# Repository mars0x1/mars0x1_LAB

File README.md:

# mars0x1_LAB — Mixed-Signal Electronics Workstation

An all-in-one, 4-layer mixed-signal laboratory instrument designed around the **ESP32-S3** microcontroller. `mars0x1_LAB` integrates a **4-channel analog oscilloscope front-end**, an **AD9833 12.5 MHz Direct Digital Synthesis (DDS) function generator**, a **dual high-speed pulse generator**, **3× rotary encoder physical user controls**, and an ultra-low-noise **100% linear split power supply**.

---

---

## ⚡ Technical Specifications

| Subsystem | Specification | Value / Details |
| :--- | :--- | :--- |
| **Physical Dimensions** | Board Size | $175.59\,\text{mm} \times 134.00\,\text{mm}$ ($6.91^{\prime\prime} \times 5.28^{\prime\prime}$) |
| | Layer Stackup | 4 Copper Layers (`F.Cu`, `In1.Cu`, `In2.Cu`, `B.Cu`) |
| | Grounding & Thermal | 4-layer solid DGND planes with **220 DGND ground stitching vias** |
| | Fabrication Rules | Min $0.25\,\text{mm}$ trace, $0.20\,\text{mm}$ clearance, $0.30\,\text{mm}$ via drill (JLCPCB-ready) |
| **Core Controller** | Microcontroller | **ESP32-S3-DEVKITC-1-N8R2** |
| | Processor | Xtensa® 32-bit LX7 dual-core up to $240\,\text{MHz}$ |
| | Memory & Wireless | 8 MB Octal Flash, 2 MB PSRAM, Wi-Fi 4 (802.11 b/g/n), Bluetooth® 5 (LE) |
| | Host Interface | Dual USB-C: Native USB-OTG high-speed telemetry + CP2102/CH343 UART programming |
| **4-Channel Oscilloscope** | Channels | 4 Independent BNC Inputs (`CH 1`, `CH 2`, `CH 3`, `CH 4`) |
| | Analog Buffer | `U6` (`OPA4192IPWR`) — Precision Rail-to-Rail I/O, $10\,\text{MHz}$ GBW, $20\,\text{V}/\mu\text{s}$ slew rate, $5.5\,\text{nV}/\sqrt{\text{Hz}}$ ultra-low noise |
| | Precision Reference | `U10` (`REF3025AIDBZT`) — $2.50\,\text{V}$ voltage reference ($50\,\text{ppm}/^\circ\text{C}$) |
| | Input Protection | 4× $1\,\text{k}\Omega$ series current limiters (`R32`–`R35`) + 4× `BAT54S` Schottky clamping diodes (`D9`–`D12`) to $3.3\,\text{V}$ & DGND |
| **DDS Function Generator** | Core IC | Analog Devices AD9833 (28-bit frequency accumulator, $0.1\,\text{Hz}$ to $12.5\,\text{MHz}$) |
| | Module Sockets | Dual parallel female headers (`J5` Standard & `J12` Swapped CS/SDATA pinout) |
| | Waveforms | Sine, Triangle, Square (programmable via SPI) |
| | Output Driver | `U20` (`MCP4131`) digital potentiometer + `U9` (`TL071`) buffer + `TIP31C`/`TIP32C` complementary push-pull driver capable of driving $50\,\Omega$ loads |
| **Dual Pulse Generator** | Outputs | `PULSE 1` (`J11`) and `PULSE 2` (`J10`) via $75\,\Omega$ BNC connectors |
| | Drivers | Discrete NPN emitter-follower buffers (`Q1`, `Q4` `2N3904`) powered by $+5\,\text{V}$ |
| | Duty & Width | ESP32 hardware timers (MCPWM/LEDC) on clean GPIOs 47 & 21 |
| | Amplitude Control | `U8` (`MCP4131`) digital potentiometer + $1\,\text{k}\Omega$ emitter pull-downs (`R36`, `R37`) |
| **Front Panel Controls** | Rotary Encoders | 3× ALPS EC11 Encoders with Push Switches (`U17` TIME, `U18` VOLT, `U19` MENU) |
| **Power Supply (100% Linear)** | AC Input | 3-terminal pads (`J6`, `J7`, `J8`) for external center-tapped $12\text{V}-0-12\text{V}$ AC transformer secondary |
| | Rectification & Bulk | 6A full-wave bridge rectifier (`D1`–`D4` `6A10`) + $4000\,\mu\text{F}$ reservoir (`C1`–`C4`) |
| | Voltage Regulators | $+12\,\text{V}$ (`LM7812`), $-12\,\text{V}$ (`LM7912`), $+5\,\text{V}$ (`LM7805`) |
| | Noise & Ripple | Zero switching hash, pure analog linear regulation |

---

## 🎛️ Front Panel & Connector Mapping

All front-panel connectors along the bottom edge ($Y \approx 185.5\,\text{mm}$) are clearly ordered and labeled on the silkscreen from left to right:

```
+----------------------------------------------------------------------------------------------------+
|  [J11]       [J10]       [J9]          [U19]         [U18]         [U17]     [J1]   [J2]   [J3]   [J4]   |
| PULSE 1     PULSE 2    DDS OUT     ENC 3 (MENU)  ENC 2 (VOLT)  ENC 1 (TIME)  CH 1   CH 2   CH 3   CH 4   |
+----------------------------------------------------------------------------------------------------+
```

---

## 🔌 Power & Safety Instructions

> [!IMPORTANT]
> **External Low-Voltage AC Transformer Only — DO NOT CONNECT MAINS (120V / 240V)!**
> * Terminals `J6`, `J7`, and `J8` connect exclusively to the **low-voltage secondary side** of an external center-tapped transformer ($12\text{V}-0-12\text{V}$ AC, 20VA to 50VA).
> * `J8` = `~12V AC` (Secondary Leg 1)
> * `J7` = `0V CT` (Secondary Center Tap / Earth DGND)
> * `J6` = `~12V AC` (Secondary Leg 2)
> * The ESP32 DevKit is powered via USB Type-C from your host PC.

> [!WARNING]
> **TO-220 Tab Isolation:**
> * `LM7812` & `LM7805` tabs are connected to **DGND**.
> * `LM7912` tab is connected to **$-18\,\text{V}$ DC raw input**, NOT ground!
> * `TIP31C` & `TIP32C` tabs are connected to $+12\text{V}$ and $-12\text{V}$ collectors.
> * Always use **individual clip-on heatsinks** or insulating Sil-Pads and shoulder washers if mounting to a shared metal bracket.

---

## 📁 Repository Structure

```text
mars0x1_LAB/
├── assets/
│   ├── pcb_3d_render.png          # High-resolution 3D raytraced preview
│   ├── pcb_front.svg              # Top copper and silkscreen vector
│   ├── pcb_back.svg               # Bottom copper and silkscreen vector
│   ├── schematic_diagram.svg      # A3 schematic vector export
│   └── schematic.pdf              # Full production schematic PDF
├── gerbers/                       # Raw RS-274X Gerber & Excellon drill files
├── gerbers.zip                    # Ready-to-upload archive for JLCPCB
├── mars0x1_LAB.kicad_pro          # KiCad 9 Project file
├── mars0x1_LAB.kicad_sch          # KiCad 9 Schematic
├── mars0x1_LAB.kicad_pcb          # KiCad 9 PCB Layout
├── .gitignore
├── LICENSE                        # MIT License
└── README.md
```

---

## 🛠️ How to Order on JLCPCB

1. Download [`gerbers.zip`](gerbers.zip).
2. Go to [JLCPCB.com](https://jlcpcb.com) and click **Order Now**.
3. Drag and drop `gerbers.zip`.
4. Choose the following standard parameters:
   * **Layers:** 4
   * **Dimensions:** $175.59 \times 134.00\,\text{mm}$ (auto-detected)
   * **PCB Thickness:** 1.6 mm
   * **PCB Color:** Green / Blue / Black / Purple (user choice)
   * **Surface Finish:** HASL with lead (or ENIG for gold-plated pads)
   * **Copper Weight:** 1 oz outer / 0.5 oz inner
5. Submit order (Total cost for 5 boards fits well within the **$100 Hack Club OnBoard grant**).

---

## 📜 Credits & License

* **Designed by:** `mars0x1`
* **Sponsorship:** Built with support from [Hack Club](https://hackclub.com).
* **License:** [MIT License](LICENSE).

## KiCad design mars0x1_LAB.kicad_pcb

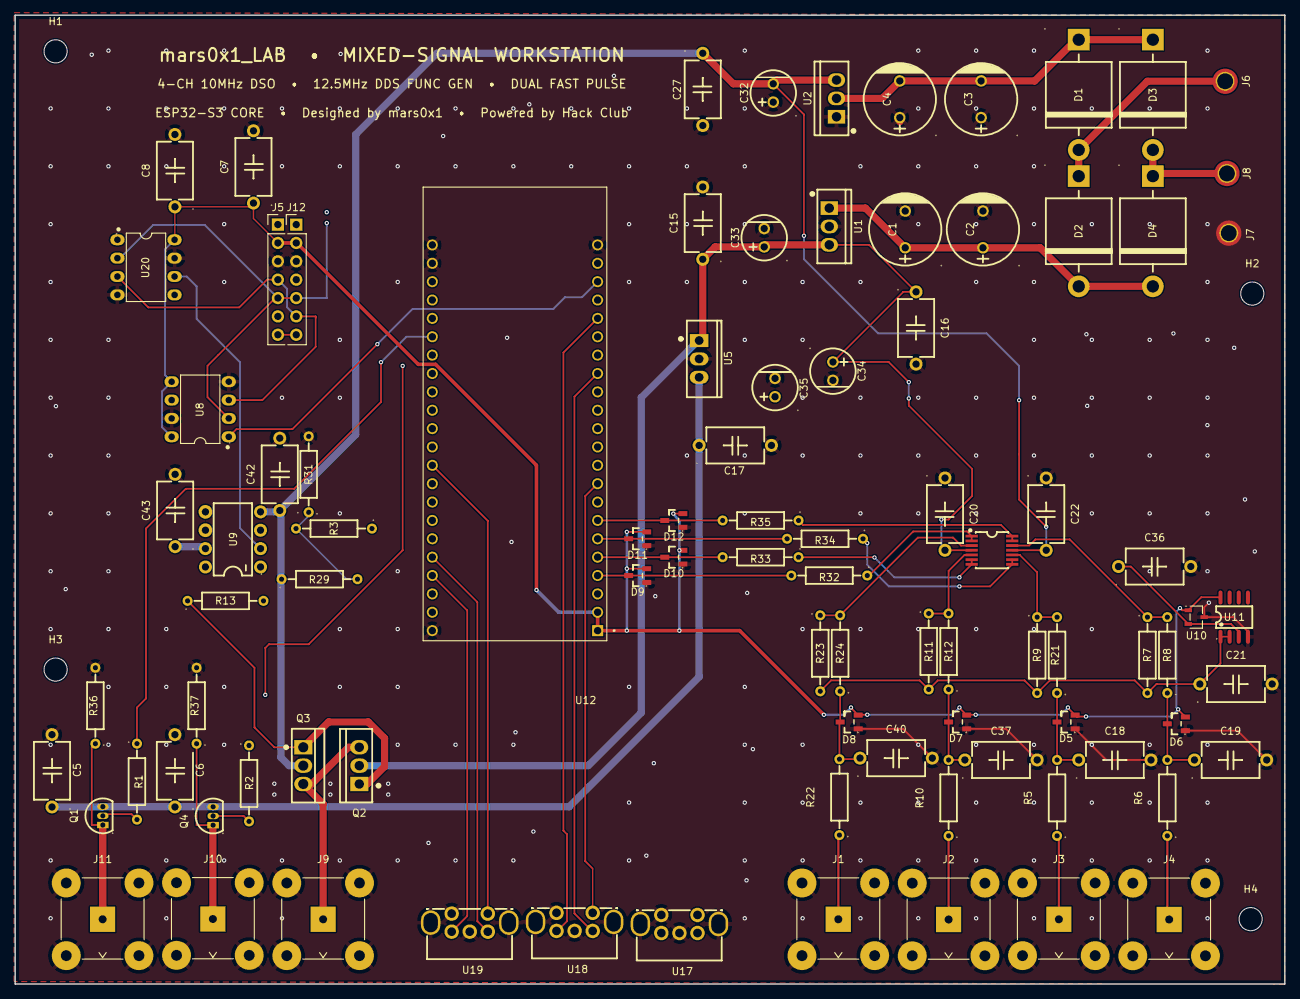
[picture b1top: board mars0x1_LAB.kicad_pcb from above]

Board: 4 copper layers, 175.6 x 134.0 mm, 95 parts (0 on the bottom side), 57 nets.

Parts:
C1, C2, C3, C4: 01EC4294SHC1000UF25V; C503217_CAP-TH_BD10_0-P5_00-D1_0-FD
C5, C6, C7, C8, C15, C16, C17, C18, C19, C20, C21, C22, C27, C36, C37, C40, C42, C43: C_Small; C1620210_CAP-TH_L8_0-W5_0-P10_00-D0_6
C32, C33, C34, C35: 35ZLH100MEFC6.3X11; C109392_CAP-TH_BD6_3-P2_50-D1_0-FD
D1, D2, D3, D4: 6A10; C2461_R-6_BD9_0-L9_0-W9_0-P15_00-D1_7-FD
D5, D6, D7, D8: BAT54S_C545549; C545549_SOT-23-3_L2_9-W1_3-P1_90-LS2_4-TL
D9, D10, D11, D12: BAT54S; C545549_SOT-23-3_L2_9-W1_3-P1_90-LS2_4-TL
H1, H2, H3, H4: MountingHole_3.2mm_M3
J1: CH 1; BNC_TEConnectivity_1478035_Horizontal
J2: CH 2; BNC_TEConnectivity_1478035_Horizontal
J3: CH 3; BNC_TEConnectivity_1478035_Horizontal
J4: CH 4; BNC_TEConnectivity_1478035_Horizontal
J5: AD9833 (STD); PinHeader_1x07_P2.54mm_Vertical
J6, J8: ~12V AC; MountingHole_2.2mm_M2_ISO7380_Pad_TopBottom
J7: 0V CT; MountingHole_2.2mm_M2_ISO7380_Pad_TopBottom
J9: DDS OUT; BNC_TEConnectivity_1478035_Horizontal
J10: PULSE 2; BNC_TEConnectivity_1478035_Horizontal
J11: PULSE 1; BNC_TEConnectivity_1478035_Horizontal
J12: AD9833 (ALT); PinHeader_1x07_P2.54mm_Vertical
Q1, Q4: 2N3904; C118538_TO-92-3_L5_1-W4_1-P1_27-L
Q2: TIP31C; C13506_TO-220-3_L10_0-W4_5-P2_54-T
Q3: TIP32C; C75057_TO-220AB-3_L10_4-W4_6-P2_54-T
R1, R2: MF1/4W-1KΩ±1% T52; C119353_RES-TH_BD2_3-L6_5-P10_50-D0_5
R3, R5, R6, R8, R10, R12, R21, R22, R24: MF1/4W-100KΩ±1% T52; C119369_RES-TH_BD2_3-L6_5-P10_50-D0_5
R7, R9, R11, R23, R31: MF1/4W-20KΩ±1% T52; C119353_RES-TH_BD2_3-L6_5-P10_50-D0_5
R13: MF1/4W-200KΩ±1% T52; C119373_RES-TH_BD2_3-L6_5-P10_50-D0_5
R29: MF1/4W-1MΩ±1%T52; C714052_RES-TH_BD2_3-L6_5-P10_50-D0_5
R32, R33, R34, R35, R36, R37: 1k; C119353_RES-TH_BD2_3-L6_5-P10_50-D0_5
U1: LM7812 (+12V); C7432223_TO-220-3_L10_0-W4_6-P2_54-L
U2: LM7912 (-12V); C7432211_TO-220-3_L10_0-W4_6-P2_54-L
U5: LM7805 (+5V); C725349_TO-220-3_L10_0-W4_5-P2_54-L
U6: OPA4192IPWR; C2057935_TSSOP-14_L5_0-W4_4-P0_65-LS6_4-TL
U8, U20: MCP4131-104E/P; C640354_PDIP-8_L9_3-W6_4-P2_54-LS7_9-BL-1
U9: TL071CP; C273645_PDIP-8_L9_6-W6_4-P2_54-LS7_6-BL
U10: REF3025AIDBZT; C96625_SOT-23-3_L3_0-W1_7-P0_95-LS2_9-BR
U11: TLV9062IDR; C398355_SOIC-8_L5_0-W4_0-P1_27-LS6_0-BL
U12: ESP32-S3-DEVKITC-1-N8R2; XCVR_ESP32-S3-DEVKITC-1-N8R2
U17: ENC 1 (TIME); C2830185_SW-TH_EC11B1524XX
U18: ENC 2 (VOLT); C2830185_SW-TH_EC11B1524XX
U19: ENC 3 (MENU); C2830185_SW-TH_EC11B1524XX

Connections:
2.5V: C21.1, R7.2, R9.2, R11.2, R23.2, U11.1 (OUTA), U11.2 (INA-)
3.3V: C7.1, C8.1, D5.2 (A), D6.2 (A), D7.2 (A), D8.2 (A), D9.2 (A), D10.2 (A), D11.2 (A), D12.2 (A), J5.2, J12.2, U8.5 (P0A), U8.8 (VDD), U10.1 (IN), U11.8 (VCC), U12.J1_1 (3V3), U12.J1_2 (3V3), U20.8 (VDD)
+5V: C5.1, C6.1, C17.1, C35.1, Q1.3 (C), Q4.3 (C), U5.3 (OUTPUT)
+12: C15.1, C16.1, C20.2, C33.1, C34.1, C43.1, Q2.2 (C), U1.3 (VOUT), U5.1 (INPUT), U6.4 (V+), U9.7 (VCC+)
+12AC: D3.2 (K), D4.1 (A), J8.1
-12AC: D1.2 (K), D2.1 (A), J6.1
-12V: C22.2, C27.1, C32.2, C42.1, Q3.2 (C), R29.1, U2.3 (OUT), U6.11 (V-), U9.4 (VCC-)
Amplitude: R13.2, U9.2 (IN-), U20.6 (P0W)
CH1_BUF: R32.1, U6.1 (OUTA), U6.2 (-INA)
CH2_BUF: R33.1, U6.6 (-INB), U6.7 (OUTB)
CH3_BUF: R34.1, U6.8 (OUTC), U6.9 (-INC)
CH4_BUF: R35.1, U6.13 (-IND), U6.14 (OUTD)
CH-1: D9.3 (2), R32.2, U12.J1_4 (GPIO4)
CH-2: D10.3 (2), R33.2, U12.J1_5 (GPIO5)
CH-3: D11.3 (2), R34.2, U12.J1_6 (GPIO6)
CH-4: D12.3 (2), R35.2, U12.J1_7 (GPIO7)
DGND: C1.2, C2.2, C3.1, C4.1, C5.2, C6.2, C7.2, C8.2, C15.2, C16.2, C17.2, C18.2, C19.2, C20.1, C21.2, C22.1, C27.2, C32.1, C33.2, C34.2, C35.2, C36.2, C37.2, C40.2, C42.2, C43.2, D5.1 (A), D6.1 (A), D7.1 (A), D8.1 (A), D9.1 (A), D10.1 (A), D11.1 (A), D12.1 (A), J1.2, J2.2, J3.2, J4.2, J5.3, J7.1, J9.2, J10.2, J11.2, J12.3, R31.2, R36.2, R37.2, U1.2 (GND), U2.1 (GND), U5.2 (GND), U8.4 (VSS), U8.7 (P0B), U10.3 (GND), U11.4 (VEE/GND), U12.J1_22 (GND), U12.J3_1 (GND), U12.J3_21 (GND), U12.J3_22 (GND), U17.C, U17.D, U17.EH, U18.C, U18.D, U18.EH, U19.C, U19.D, U19.EH, U20.4 (VSS), U20.7 (P0B)
GPIO 1: U12.J3_4 (GPIO1), U19.A
GPIO 2: U12.J3_5 (GPIO2), U19.B
GPIO 8: U12.J1_12 (GPIO8), U17.E
GPIO 9: U12.J1_15 (GPIO9), U18.B
GPIO 10: J5.6, J12.4, U12.J1_16 (GPIO10)
GPIO 11: J5.4, J12.6, U8.3 (SDI/SDO), U12.J1_17 (GPIO11), U20.3 (SDI/SDO)
GPIO 12: U12.J1_18 (GPIO12), U18.A
GPIO 13: J5.5, J12.5, U8.2 (SCK), U12.J1_19 (GPIO13), U20.2 (SCK)
GPIO 14: U8.1 (CS#), U12.J1_20 (GPIO14)
GPIO 15: U12.J1_8 (GPIO15), U20.1 (CS#)
GPIO 16: U12.J1_9 (GPIO16), U18.E
GPIO 17: U12.J1_10 (GPIO17), U17.A
GPIO 18: U12.J1_11 (GPIO18), U17.B
GPIO 21: R2.1, U12.J3_18 (GPIO21)
GPIO 38: U12.J3_10 (GPIO38), U19.E
GPIO 47: R1.1, U12.J3_17 (GPIO47)
INA+: R23.1, R24.2, U6.3 (+INA)
INB+: R11.1, R12.2, U6.5 (+INB)
INC+: R9.1, R21.2, U6.10 (+INC)
IND+: R7.1, R8.2, U6.12 (+IND)
unnamed: C3.2, C4.2, D1.1 (A), D3.1 (A), U2.2 (IN)
unnamed: C1.1, C2.1, D2.2 (K), D4.2 (K), U1.1 (VCC)
unnamed: C18.1, D5.3 (2), R5.2, R21.1
unnamed: C19.1, D6.3 (2), R6.2, R8.1
unnamed: C37.1, D7.3 (2), R10.2, R12.1
unnamed: C40.1, D8.3 (2), R22.2, R24.1
unnamed: J3.1, R5.1
unnamed: J4.1, R6.1
unnamed: J2.1, R10.1
unnamed: J1.1, R22.1
unnamed: J5.7, J12.7, U20.5 (P0A)
unnamed: Q1.2 (B), R1.2
unnamed: J11.1, Q1.1 (E), R36.1
unnamed: Q2.1 (B), Q3.1 (B), R13.1, U9.6 (OUT)
unnamed: J9.1, Q2.3 (E), Q3.3 (E)
unnamed: Q4.2 (B), R2.2
unnamed: J10.1, Q4.1 (E), R37.1
unnamed: R3.1, U8.6 (P0W)
unnamed: R3.2, R29.2, R31.1, U9.3 (IN+)
ref: C36.1, U10.2 (OUT), U11.3 (INA+)

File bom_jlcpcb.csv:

Comment,Designator,Footprint,LCSC Part #
"01EC4294SHC1000UF25V","C3 C4 C1 C2","C503217_CAP-TH_BD10_0-P5_00-D1_0-FD","C503217"
"35ZLH100MEFC6.3X11","C34 C33 C35 C32","C109392_CAP-TH_BD6_3-P2_50-D1_0-FD","C109392"
"C_Small","C36 C16 C8 C6 C27 C20 C21 C37 C22 C42 C19 C40 C7 C17 C43 C18 C15 C5","C1620210_CAP-TH_L8_0-W5_0-P10_00-D0_6","C1620210"
"BAT54S","D10 D9 D11 D12","C545549_SOT-23-3_L2_9-W1_3-P1_90-LS2_4-TL","C545549"
"6A10","D3 D1 D4 D2","C2461_R-6_BD9_0-L9_0-W9_0-P15_00-D1_7-FD","C2461"
"BAT54S_C545549","D6 D7 D5 D8","C545549_SOT-23-3_L2_9-W1_3-P1_90-LS2_4-TL","C545549"
"CH 1","J1","BNC_TEConnectivity_1478035_Horizontal",""
"PULSE 2","J10","BNC_TEConnectivity_1478035_Horizontal",""
"PULSE 1","J11","BNC_TEConnectivity_1478035_Horizontal",""
"AD9833 (ALT)","J12","PinHeader_1x07_P2.54mm_Vertical",""
"CH 2","J2","BNC_TEConnectivity_1478035_Horizontal",""
"CH 3","J3","BNC_TEConnectivity_1478035_Horizontal",""
"CH 4","J4","BNC_TEConnectivity_1478035_Horizontal",""
"AD9833 (STD)","J5","PinHeader_1x07_P2.54mm_Vertical",""
"~12V AC","J6 J8","MountingHole_2.2mm_M2_ISO7380_Pad_TopBottom",""
"0V CT","J7","MountingHole_2.2mm_M2_ISO7380_Pad_TopBottom",""
"DDS OUT","J9","BNC_TEConnectivity_1478035_Horizontal",""
"2N3904","Q1 Q4","C118538_TO-92-3_L5_1-W4_1-P1_27-L","C118538"
"TIP31C","Q2","C13506_TO-220-3_L10_0-W4_5-P2_54-T","C13506"
"TIP32C","Q3","C75057_TO-220AB-3_L10_4-W4_6-P2_54-T","C75057"
"MF1/4W-200KΩ±1% T52","R13","C119373_RES-TH_BD2_3-L6_5-P10_50-D0_5","C119373"
"MF1/4W-1KΩ±1% T52","R2 R1","C119353_RES-TH_BD2_3-L6_5-P10_50-D0_5","C119353"
"MF1/4W-1MΩ±1%T52","R29","C714052_RES-TH_BD2_3-L6_5-P10_50-D0_5","C714052"
"MF1/4W-20KΩ±1% T52","R31 R23 R11 R9 R7","C119353_RES-TH_BD2_3-L6_5-P10_50-D0_5","C119353"
"1k","R32 R36 R34 R35 R33 R37","C119353_RES-TH_BD2_3-L6_5-P10_50-D0_5","C119353"
"MF1/4W-100KΩ±1% T52","R6 R12 R22 R24 R3 R21 R10 R8 R5","C119369_RES-TH_BD2_3-L6_5-P10_50-D0_5","C119369"
"LM7812 (+12V)","U1","C7432223_TO-220-3_L10_0-W4_6-P2_54-L","C7432223"
"REF3025AIDBZT","U10","C96625_SOT-23-3_L3_0-W1_7-P0_95-LS2_9-BR","C96625"
"TLV9062IDR","U11","C398355_SOIC-8_L5_0-W4_0-P1_27-LS6_0-BL","C398355"
"ESP32-S3-DEVKITC-1-N8R2","U12","XCVR_ESP32-S3-DEVKITC-1-N8R2",""
"ENC 1 (TIME)","U17","C2830185_SW-TH_EC11B1524XX","C2830185"
"ENC 2 (VOLT)","U18","C2830185_SW-TH_EC11B1524XX","C2830185"
"ENC 3 (MENU)","U19","C2830185_SW-TH_EC11B1524XX","C2830185"
"LM7912 (-12V)","U2","C7432211_TO-220-3_L10_0-W4_6-P2_54-L","C7432211"
"LM7805 (+5V)","U5","C725349_TO-220-3_L10_0-W4_5-P2_54-L","C725349"
"OPA4192IPWR","U6","C2057935_TSSOP-14_L5_0-W4_4-P0_65-LS6_4-TL","C2057935"
"MCP4131-104E/P","U8 U20","C640354_PDIP-8_L9_3-W6_4-P2_54-LS7_9-BL-1","C640354"
"TL071CP","U9","C273645_PDIP-8_L9_6-W6_4-P2_54-LS7_6-BL","C273645"
